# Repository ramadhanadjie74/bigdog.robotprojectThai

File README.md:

BIG DOG PROJEK AT CRRU, CHIANG-RAI RAJABHAT, THAILAND.
Dalam projek ini saya berpersan sebagai software developer/programmer
Saya sebagai penanggung jawab team yang terdiri dari 3 orang (termasuk saya).
.
BIGDOG adalah robot anjing yang bereperan sebagai robot penghibur pasien anak-anak di rumah sakit.
Robot ini dapat bergerak ke 8 arah :
- DEPAN
- BELAKANG
- KIRI
- KANAN
- SERONG KANAN DEPAN
- SERONG KIRI DEPAN
- SERONG KANAN BELAKANG
- SERONG KIRI BELAKANG
dan memiliki fungsi untuk menampilkan beberapa display emosi :
- SENANG
- SEDIH
- MARAH
- dan beberapa emosi lainnya
Program IDE yang digunakan adalah QTCreator. Dengan Bahasa C+.
ROBOT mempunyai 4 motor penggerak, 1 OrangePi. Robot dikendalikan menggunakan CONTROLLER GUI yang diremote ke orangePI melalui notebook.
.

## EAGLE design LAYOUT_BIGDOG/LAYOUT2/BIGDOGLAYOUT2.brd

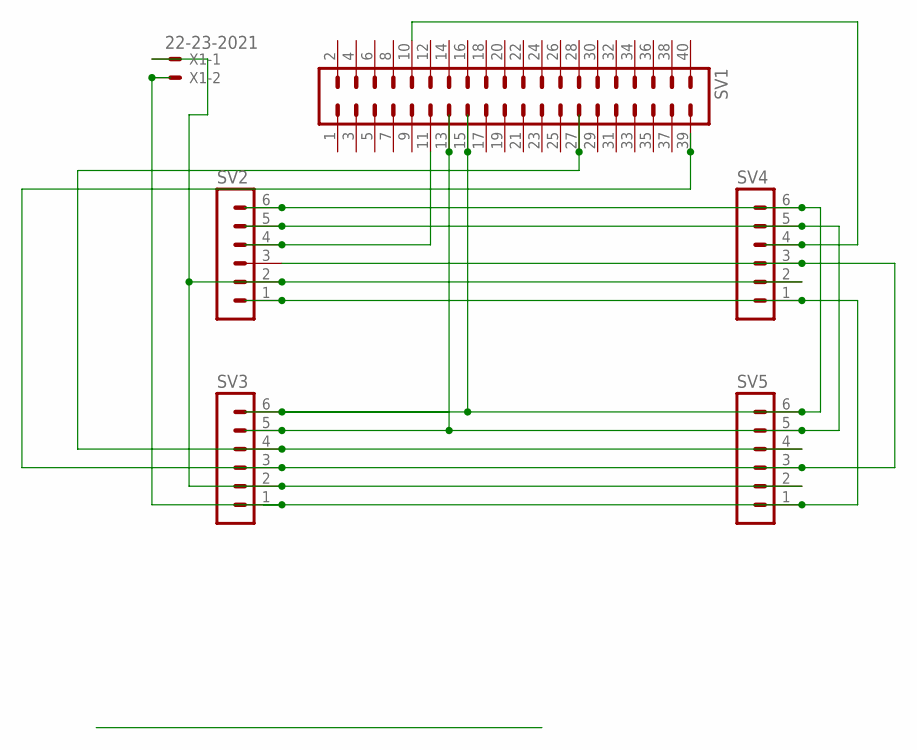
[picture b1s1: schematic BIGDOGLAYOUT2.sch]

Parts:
SV1: MA20-2
SV2, SV3, SV4, SV5: MA06-1
X1: 22-23-2021

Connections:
unnamed: SV1.11, SV2.4
unnamed: SV1.10, SV4.4
unnamed: SV2.2, SV3.2, SV4.2, SV5.2, X1.1
unnamed: SV1.15, SV2.6, SV3.6, SV4.6, SV5.6
unnamed: SV1.27, SV3.4, SV5.4
unnamed: SV1.39, SV2.3, SV3.3, SV4.3, SV5.3
unnamed: SV1.13, SV2.5, SV3.5, SV4.5, SV5.5
unnamed: SV2.1, SV3.1, SV4.1, SV5.1, X1.2

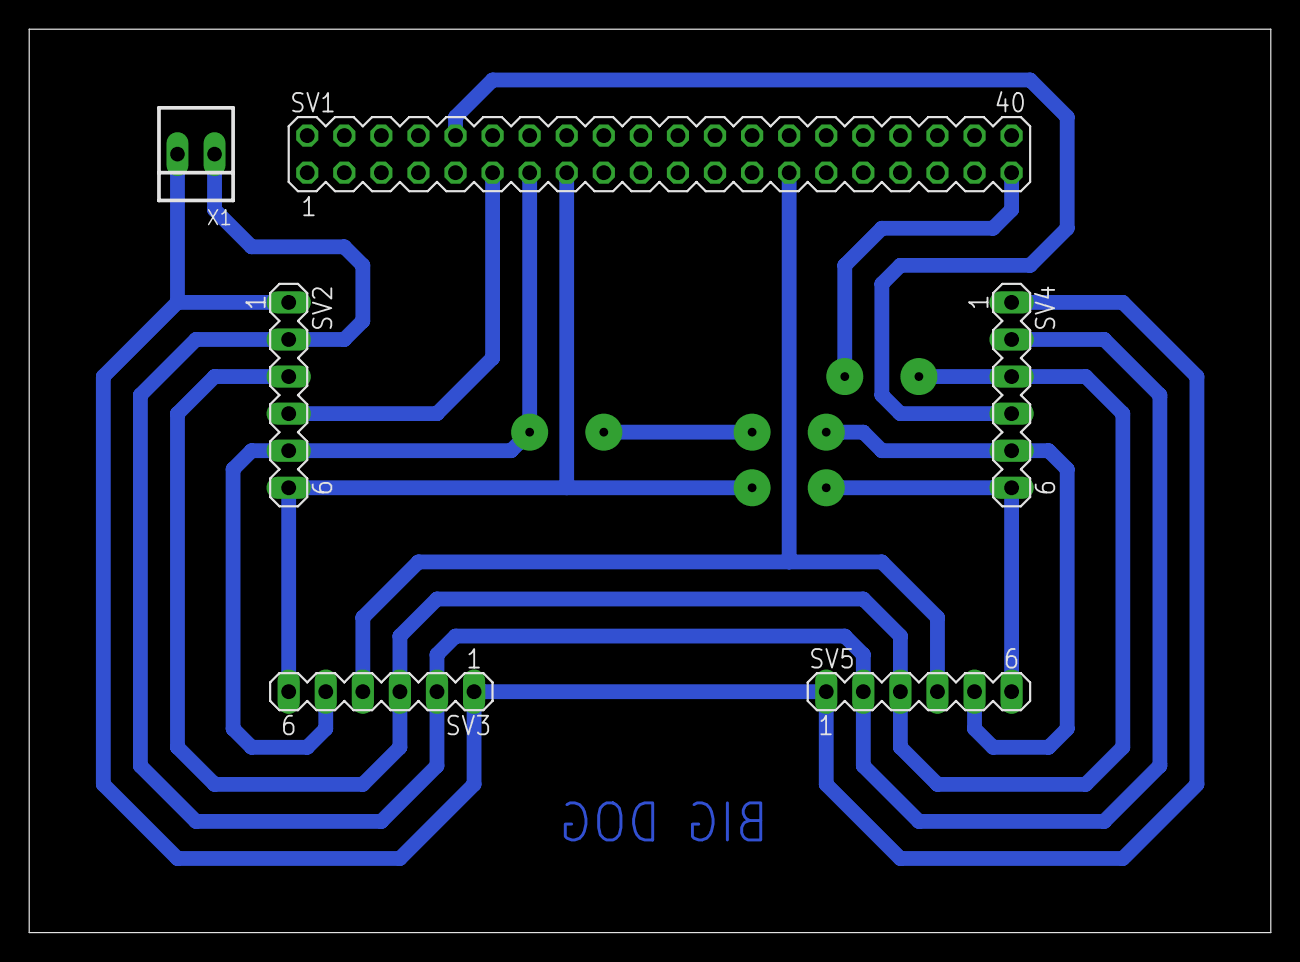
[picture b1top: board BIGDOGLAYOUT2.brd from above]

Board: 2 copper layers, 85.1 x 61.9 mm, 6 parts (0 on the bottom side), 8 nets.

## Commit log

2021-07-14 Projek Thailand CRRU BIGDOG (MIROT)
2021-07-14 PENJELASAN PROJEK
    PENJELASAN PROJEK BIGDOG - CRRU, THAILAND
2021-07-14 dokumentasi projek
    video tidak dapat diupload. lebih dari 25mb
